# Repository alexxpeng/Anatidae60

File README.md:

# Anatidae60
 Custom 60%Keyboard Atmega32u4

 QMK Firmware Steps
 Linux VM -> clone qmk-firmware
 make new directory under /keyboards
 edit config.h, KEYBNAME.h, keymap/default/keymap.c

 qmk compile
 send .hex to windows
 run qmk toolbox with .hex

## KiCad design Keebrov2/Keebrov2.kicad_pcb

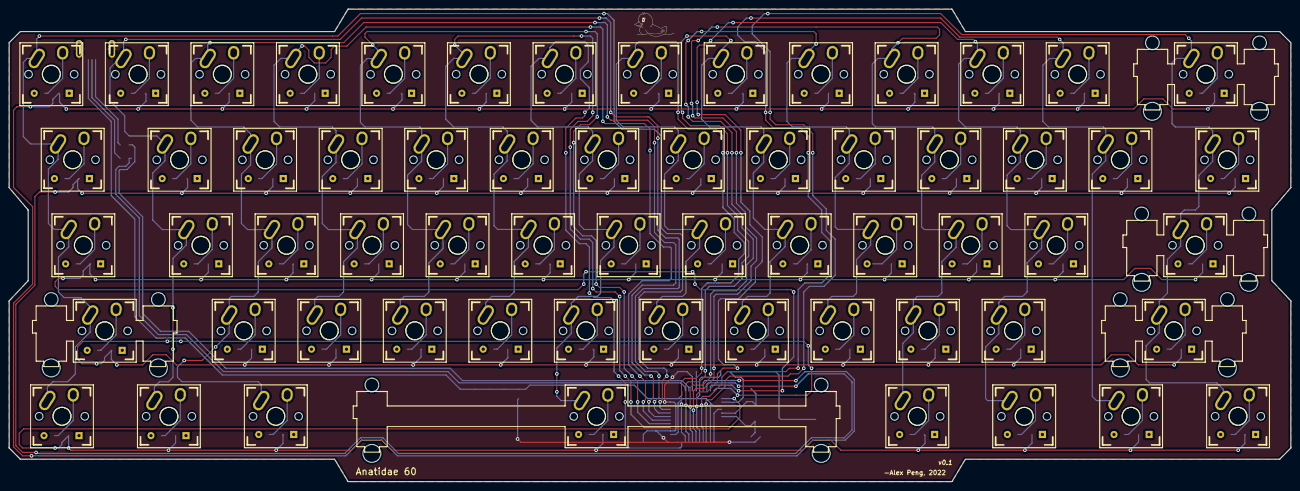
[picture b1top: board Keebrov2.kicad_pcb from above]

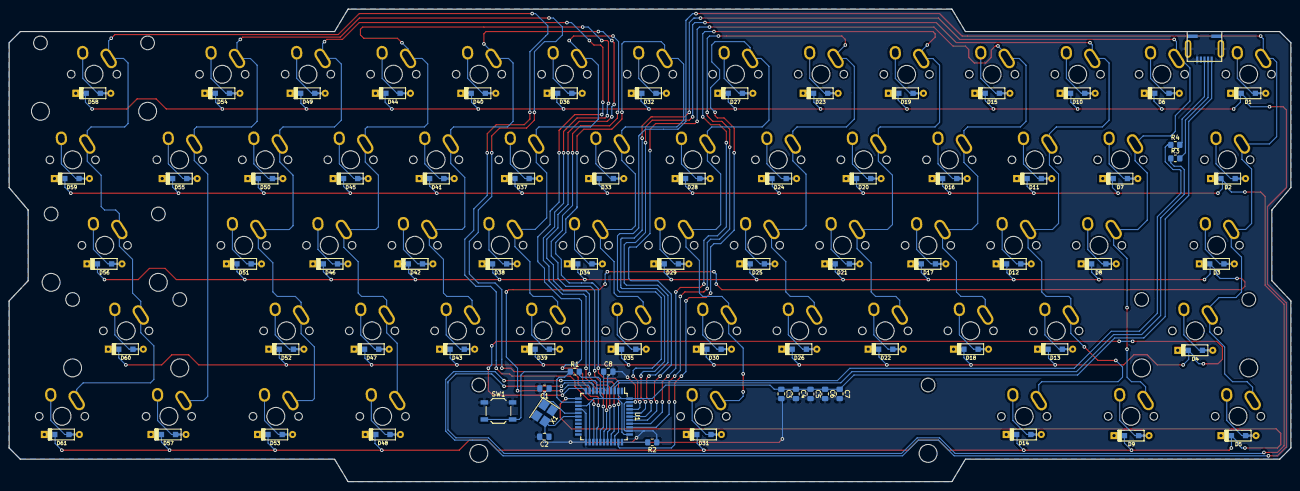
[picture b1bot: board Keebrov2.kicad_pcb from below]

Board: 2 copper layers, 285.5 x 105.2 mm, 138 parts (77 on the bottom side), 91 nets.

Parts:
C1, C2: 22p; C_0805_2012Metric_Pad1.18x1.45mm_HandSolder
C3, C4, C5, C6: 0.1u; C_0805_2012Metric_Pad1.18x1.45mm_HandSolder
C7: 4.7u; C_0805_2012Metric_Pad1.18x1.45mm_HandSolder
C8: 1u; C_0805_2012Metric_Pad1.18x1.45mm_HandSolder
D1, D2, D3, D4, D5, D6, D7, D8, D9, D10, D11, D12, D13, D14, D15, D16, D17, D18, D19, D20, D21, D22, D23, D24, D25, D26, D27, D28, D29, D30, D31, D32, D33, D34, D35, D36, D37, D38, D39, D40, D41, D42, D43, D44, D45, D46, D47, D48, D49, D50, D51, D52, D53, D54, D55, D56, D57, D58, D59, D60, D61: D; D_SOD123_axial
J1: USB_mini_micro_B; USB_miniB_hirose_5S8
K1, K6, K7, K8, K10, K11, K12, K13, K15, K16, K17, K18, K19, K20, K21, K22, K23, K24, K25, K26, K27, K28, K29, K30, K32, K33, K34, K35, K36, K37, K38, K39, K40, K41, K42, K43, K44, K45, K46, K47, K49, K50, K51, K52, K54, K55: KEYSW; Mx_Alps_100
K2, K59: KEYSW; Mx_Alps_150
K3: KEYSW; Mx_Alps_175
K4, K56: KEYSW; Mx_Alps_225
K5, K9, K14, K48, K53, K57, K61: KEYSW; Mx_Alps_125
K31: KEYSW; Mx_Alps_625
K58: KEYSW; Mx_Alps_200
K60: KEYSW; Mx_Alps_275
R1, R2: 10k; R_0805_2012Metric_Pad1.20x1.40mm_HandSolder
R3, R4: 22; R_0805_2012Metric_Pad1.20x1.40mm_HandSolder
SW1: SW_PUSH; SW_SPST_TL3342
U1: ATMEGA32U4; TQFP-44_10x10mm_Pitch0.8mm
X1: XTAL_GND; Crystal_SMD_SeikoEpson_FA238-4Pin_3.2x2.5mm_HandSoldering

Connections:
/col0: K1.1, K2.1, K3.1, K4.1, K5.1, U1.41
/col1: K6.1, K7.1, K8.1, K9.1, U1.40
/col2: K10.1, K11.1, K12.1, K13.1, K14.1, U1.39
/col3: K15.1, K16.1, K17.1, K18.1, U1.38
/col4: K19.1, K20.1, K21.1, K22.1, U1.37
/col5: K23.1, K24.1, K25.1, K26.1, U1.36
/col6: K27.1, K28.1, K29.1, K30.1, K31.1, U1.32
/col7: K32.1, K33.1, K34.1, K35.1, U1.31
/col8: K36.1, K37.1, K38.1, K39.1, U1.30
/col9: K40.1, K41.1, K42.1, K43.1, U1.29
/col10: K44.1, K45.1, K46.1, K47.1, K48.1, U1.28
/col11: K49.1, K50.1, K51.1, K52.1, K53.1, U1.27
/col12: K54.1, K55.1, K57.1, U1.26
/col13: K56.1, K58.1, K59.1, K60.1, K61.1, U1.25
/row0: D1.1, D6.1, D10.1, D15.1, D19.1, D23.1, D27.1, D32.1, D36.1, D40.1, D44.1, D49.1, D54.1, D58.1, U1.8
/row1: D2.1, D7.1, D11.1, D16.1, D20.1, D24.1, D28.1, D33.1, D37.1, D41.1, D45.1, D50.1, D55.1, D59.1, U1.9
/row2: D3.1, D8.1, D12.1, D17.1, D21.1, D25.1, D29.1, D34.1, D38.1, D42.1, D46.1, D51.1, D56.1, U1.10
/row3: D4.1, D13.1, D18.1, D22.1, D26.1, D30.1, D35.1, D39.1, D43.1, D47.1, D52.1, D60.1, U1.11
/row4: D5.1, D9.1, D14.1, D31.1, D48.1, D53.1, D57.1, D61.1, U1.12
GND: C1.2, C2.2, C3.2, C4.2, C5.2, C6.2, C7.2, C8.2, J1.5, J1.6, R2.1, SW1.1, U1.5, U1.15, U1.23, U1.35, U1.43, X1.3
unnamed: C1.1, U1.16, X1.1
unnamed: C2.1, U1.17, X1.2
unnamed: C8.1, U1.6
unnamed: D1.2, K1.2
unnamed: D2.2, K2.2
unnamed: D3.2, K3.2
unnamed: D4.2, K4.2
unnamed: D5.2, K5.2
unnamed: D6.2, K6.2
unnamed: D7.2, K7.2
unnamed: D8.2, K8.2
unnamed: D9.2, K9.2
unnamed: D10.2, K10.2
unnamed: D11.2, K11.2
unnamed: D12.2, K12.2
unnamed: D13.2, K13.2
unnamed: D14.2, K14.2
unnamed: D15.2, K15.2
unnamed: D16.2, K16.2
unnamed: D17.2, K17.2
unnamed: D18.2, K18.2
unnamed: D19.2, K19.2
unnamed: D20.2, K20.2
unnamed: D21.2, K21.2
unnamed: D22.2, K22.2
unnamed: D23.2, K23.2
unnamed: D24.2, K24.2
unnamed: D25.2, K25.2
unnamed: D26.2, K26.2
unnamed: D27.2, K27.2
unnamed: D28.2, K28.2
unnamed: D29.2, K29.2
unnamed: D30.2, K30.2
unnamed: D31.2, K31.2
unnamed: D32.2, K32.2
unnamed: D33.2, K33.2
unnamed: D34.2, K34.2
unnamed: D35.2, K35.2
unnamed: D36.2, K36.2
unnamed: D37.2, K37.2
unnamed: D38.2, K38.2
unnamed: D39.2, K39.2
unnamed: D40.2, K40.2
unnamed: D41.2, K41.2
unnamed: D42.2, K42.2
unnamed: D43.2, K43.2
unnamed: D44.2, K44.2
unnamed: D45.2, K45.2
unnamed: D46.2, K46.2
unnamed: D47.2, K47.2
unnamed: D48.2, K48.2
unnamed: D49.2, K49.2
unnamed: D50.2, K50.2
unnamed: D51.2, K51.2
unnamed: D52.2, K52.2
unnamed: D53.2, K53.2
unnamed: D54.2, K54.2
unnamed: D55.2, K55.2
unnamed: D56.2, K56.2
unnamed: D57.2, K57.2
unnamed: D58.2, K58.2
unnamed: D59.2, K59.2
unnamed: D60.2, K60.2
unnamed: D61.2, K61.2
unnamed: J1.2, R3.2
unnamed: J1.3, R4.2
unnamed: R1.1, SW1.2, U1.13
unnamed: R2.2, U1.33
unnamed: R3.1, U1.3
unnamed: R4.1, U1.4
VCC: C3.1, C4.1, C5.1, C6.1, C7.1, J1.1, R1.2, U1.2, U1.7, U1.14, U1.24, U1.34, U1.44

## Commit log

2022-03-24 Added Files
2022-03-24 added qmk firmware files
2022-04-01 step files for 4 pieces
2022-04-16 updated firmware files and hex
